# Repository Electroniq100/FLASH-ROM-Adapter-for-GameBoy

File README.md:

# Mini version of SOP-32L FLASH to ROM Adapter for Game Boy Cartridges

This is a modified version of the SOP-32L FLASH to ROM Adapter for Game Boy Cartridges, it will fit in any cartridges without any modifications of the top shell of your cartridges.

## Compatible Flash Memory Chips

AM29F032@-#E* (4 MB)
or
AM29F016@-#E* (2 MB) Please note that for TSOP-48 version you will need to remove the 8 NC pins on each corner to get access to the pads.
```
 @ = Manufactured process technology (None = 0.5 µm, B = 0.32 µm, D = 0.23 µm)
 # = any speeds are compatible (75,90,120,150)
 E = 48-Pin Thin Small Outline Package (TSOP) Standard Pinout (TS 048)
 * = any temperature range (C = Commercial (0°C to +70°C) or I = Industrial (-40°C to +85°C))
```
*Ex: AM29F016-75EC, AM29F032B-120EI,...* 

---

## [How To - Assembly Guide](http://www.jrodrigo.net/wiki/how-to-diy-a-gameboy-flash-cartridge-with-a-rom-adapter-board/)

## Where to buy :package:
- [**OSHpark** (Mini Version SOP32 bare PCBs)](https://oshpark.com/shared_projects/QGnPTqav)

---

## License
#### Licenced under [Creative Commons - Attribution and Share Alike](https://github.com/JRodrigoTech/FLASH-ROM-Adapter-for-GameBoy/blob/master/LICENSE.md) by [J.Rodrigo](http://www.jrodrigo.net)

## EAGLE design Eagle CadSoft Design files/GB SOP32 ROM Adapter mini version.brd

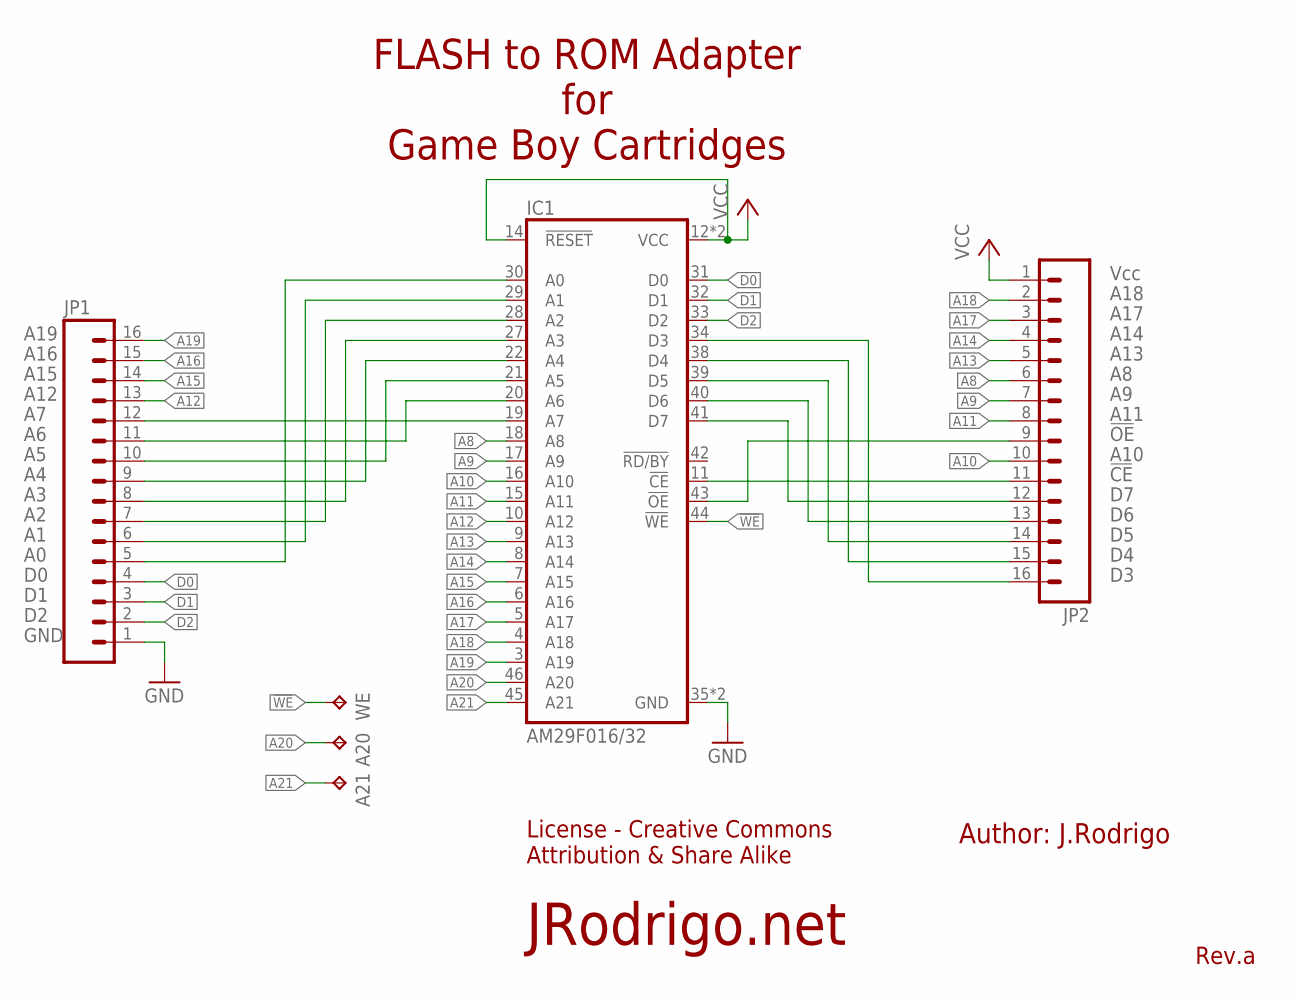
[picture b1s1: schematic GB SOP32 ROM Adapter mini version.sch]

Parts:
A20, A21: TPTP06SQ; TP06SQ
IC1: AM29F016/32; TSOP48_WITHOUT_NC
JP1, JP2: CASTELLATIONS_16-PINS*; CASTELLATIONS_16-PINS
WE: TPTP06SQ; TP06SQ

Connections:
!WE: IC1.44 (!WE), WE.TP
A8: IC1.18 (A8), JP2.6
A9: IC1.17 (A9), JP2.7
A10: IC1.16 (A10), JP2.10
A11: IC1.15 (A11), JP2.8
A12: IC1.10 (A12), JP1.13
A13: IC1.9 (A13), JP2.5
A14: IC1.8 (A14), JP2.4
A15: IC1.7 (A15), JP1.14
A16: IC1.6 (A16), JP1.15
A17: IC1.5 (A17), JP2.3
A18: IC1.4 (A18), JP2.2
A19: IC1.3 (A19), JP1.16
A20: A20.TP, IC1.46 (A20)
A21: A21.TP, IC1.45 (A21)
D0: IC1.31 (D0), JP1.4
D1: IC1.32 (D1), JP1.3
D2: IC1.33 (D2), JP1.2
GND: IC1.35 (GND), IC1.36 (GND), JP1.1
unnamed: IC1.34 (D3), JP2.16
unnamed: IC1.38 (D4), JP2.15
unnamed: IC1.39 (D5), JP2.14
unnamed: IC1.40 (D6), JP2.13
unnamed: IC1.41 (D7), JP2.12
unnamed: IC1.11 (!CE), JP2.11
unnamed: IC1.43 (!OE), JP2.9
unnamed: IC1.29 (A1), JP1.6
unnamed: IC1.28 (A2), JP1.7
unnamed: IC1.30 (A0), JP1.5
unnamed: IC1.27 (A3), JP1.8
unnamed: IC1.22 (A4), JP1.9
unnamed: IC1.21 (A5), JP1.10
unnamed: IC1.20 (A6), JP1.11
unnamed: IC1.19 (A7), JP1.12
VCC: IC1.12 (VCC), IC1.14 (!RESET), IC1.37 (VCC), JP2.1

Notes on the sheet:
A19
A16
A15
A12
GND
Vcc
A18
A17
A14
A13
A11
!OE
A10
!CE
FLASH to ROM Adapter for Game Boy Cartridges
Rev.a
Author: J.Rodrigo
License - Creative Commons Attribution & Share Alike
JRodrigo.net

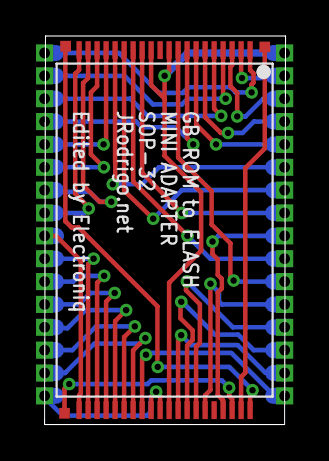
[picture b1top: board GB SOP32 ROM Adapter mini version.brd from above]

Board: 2 copper layers, 13.4 x 21.6 mm, 6 parts (0 on the bottom side), 35 nets.

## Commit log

2020-08-26 Added A20, A21 and WR names in the back
    Silk screen changes, which also include an extended information about the board in the front.
